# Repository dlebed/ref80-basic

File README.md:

# REF80 Votlage Reference Basic Test Board

REF80 is a Temperature-Controlled Buried Zener Voltage Reference with 0.05ppm/°C Drift and < 1ppm Stability.

See https://www.ti.com/product/REF80

This project is a basic breakout board to be able to test REF80.

OSH Park project available for order: https://oshpark.com/shared_projects/kTTHxNFD

## Finished Board

## Thermal Camera Captures

### Top

### Bottom

### First 2 Hours Vref at 115C

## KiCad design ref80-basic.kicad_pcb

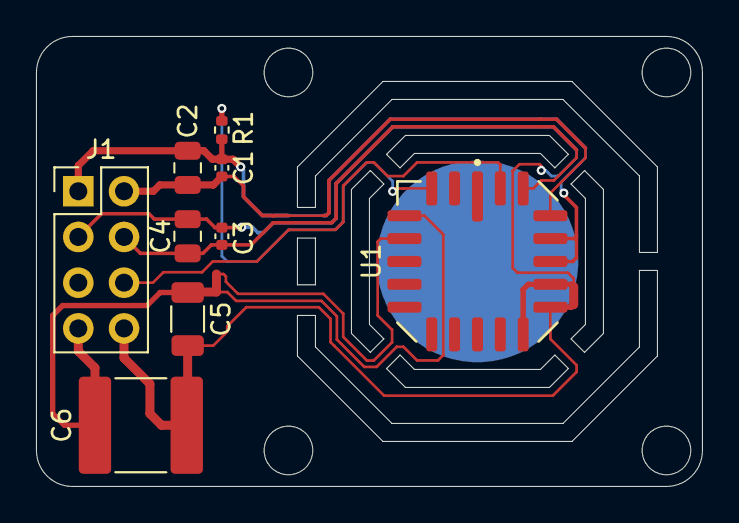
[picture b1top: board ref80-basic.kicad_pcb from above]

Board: 2 copper layers, 37.0 x 25.0 mm, 11 parts (0 on the bottom side), 9 nets.

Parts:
C1, C3: 100n; C_0402_1005Metric
C2, C4: 4u7; C_0805_2012Metric
C5: 0.47u; C_1206_3216Metric
C6: 22u 16V; C_2220_5750Metric
J1: Conn_02x04_Odd_Even; PinHeader_2x04_P2.54mm_Vertical
NT1, NT2: NetTie_2; NetTie-2_SMD_Pad0.5mm
R1: 800k; R_0402_1005Metric
U1: REF80; LCCC-20-NAJ

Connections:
/T_SET: R1.2, U1.3 (T_SET)
GND: C3.2, C4.2, J1.3, NT1.1, U1.13 (GND), U1.15 (REF_GND_F)
GNDPWR: C1.2, C2.2, J1.1, R1.1, U1.16 (HEATM), U1.17 (HEATM)
GNDREF: C5.2, C6.2, J1.8, NT1.2, U1.14 (REF_GND_S)
unnamed: NT2.2, U1.5 (REFZ_S)
OP_STBL: J1.6, U1.20 (OP_STBL)
VDC: C1.1, C2.1, J1.2, U1.18 (HEATP)
VDD: C3.1, C4.1, J1.4, U1.19 (VDD)
VREF: C5.1, C6.1, J1.7, NT2.1, U1.4 (REFZ_F)

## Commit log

2024-10-20 Initial Commit: REV.A
